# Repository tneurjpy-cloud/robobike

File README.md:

https://github.com/tneurjpy-cloud/robobike
| Supported Targets | ESP32-C3 |
| ----------------- | -------- |

ROBOBIKE: Autonomous Self-Balancing Bicycle Robot  
Copyright 2026.11.05    Masayuki Tanaami      ROBOBIKEJP    Japan  

ESP-IDF components and tools paths depend on installation location  

* Control Logic
The ROBOBIKE utilizes a dual-loop control system: an outer steering PD loop and an inner roll rate feedback loop to achieve self-balancing via counter-steering.

## Control System Architecture

```mermaid
graph TD
    %% 目標値の入力
    In((str_target)) -- "目標値" --> Sum1((+))

    subgraph OuterLoop [外側：ステアリングPD制御]
        Sum1 -- "偏差" --> GainP[Pゲイン]
        Sum1 -- "偏差" --> Diff[微分+LPF]
        
        GainP --> Sum2((+))
        Diff --> Sum2
    end

    Sum2 -- "目標ロール速度" --> Sum3((+))

    subgraph InnerLoop [内側：ロール速度FB]
        IMU[IMU_roll実測] -. "−" .-> Sum3
        Sum3 -- "偏差" --> GainW[ロールゲイン]
        GainW -- "更新量" --> Integ["積分 & 逆操舵<br>(str_out -= 更新量)"]
    end

    %% 出力とフィードバック
    Integ --> OutP[ステアリング出力 str_out]
    OutP -. "フィードバック" .-> Sum1
    
    OutP --> Limit[リミッタ]
    Limit --> PWM((PWM出力))

    %% スタイルの設定
    style OuterLoop fill:#fdfdfd,stroke:#333
    style InnerLoop fill:#f0f7ff,stroke:#0052cc
    style Integ fill:#e1f5fe,stroke:#01579b

```
## Getting Started

This project is based on "Captive Portal Example".  
Development should be done using ESP-IDF v6.0  
Please install the ESP-IDF extension in VS-Code before building this project.  
  
* How to set up IntelliSense in VS Code:  
(1) Install the ESP-IDF Extension.  
(2) (Ctrl+Shift+P)Run the command "ESP-IDF: Add vscode configuration folder".  
(3) Perform a Build to generate necessary configuration files.  
-----------------------------------------------------------  
* Settings from menuconfig are saved to \project\sdkconfig  
* Change via menuconfig, KCONFIG Name:  
    Flash size : 4MB  
    Partition Table : Custom Partition Table CSV  
        CSV file : partitions.csv  
    configUSE_TRACE_FACILITY : checked  
    configGENERATE_RUN_TIME_STATS : checked
    configTICK_RATE_HZ : 100
* For debug with GDB, delete "launch.json"
    Full Clean
    Select Target to esp32c3 via USB JTAG
    Select COM port, Build and flash
    Power down the target and perform a complete system reboot.
    OpenOCD Server, select "Eclipse CDT..."
    Full Clean
    Slelect Target to esp32c3 via USB JTAG
    Select COM port, Build and flash
    Power down the target and perform a complete system reboot.
    OpenOCD Server, select "Eclipse CDT..."
-----------------------------------------------------------  

* Change Log  
```text
Date        CODE    DATA    Description
------------------------------------------------------------------------------------------------
2026.11.10  1044       6    Chg: Fix the drift on starting, Speed-adaptive gain
2026.11.04  1043       6    Add: Check PCBA ver 06, use SPI
2026.09.27  1042       6    Add: Test mode on every reset
2026.09.13  1041       6    Dbg: Fix mobile file selection issue on OTA
2026.09.11  1040       6    Dbg: Stop servo PWM during OTA
2026.09.10  1038       6    Dbg: Accept OTA by smartphone
2026.09.02  1037       6    Chg: Captive portal handler(for iPhone)
2026.08.28  1036       6    Chg: Sleep time, minor changes for auto circling mode
2026.07.05  1033       4    Add: Data monitor and its related files.
2026.06.05  1032       4    Dbg: LED control configTICK_RATE_HZ:100
2026.05.26  1031       4    Chg: Servo PWM Rising Times. Lo-pass filter T
2026.05.19  1030    1022    Chg: Axis polarity inversion / No use GPIO Int. for Task
                            Dbg: Monitor.html  
2026.05.06  1029    1022    Chg: 3ms 1-shot soft timer -> 4ms espTimer / STR cmd Polarity +: left
                            Add: Ota, Data monitor.
                            Chg: esp-idf v5.4.1-->> v6.0.1
2026.04.07  1028    1022    Add: WiFi AP Ch. randomize
2026.03.31  1027    1021    Add: BACK cmd, SV EN Cont. heapless buffer
2026.03.20  1025    1021    Mov: GPIO definitions from servo.c to project.h
2026.03.01  1024    1021    Add: IMU data API, 
                            Dbg: Calibration
2026.02.09  1023    1021    Add: Auto circling On/Off, restore SLEEP function
2026.01.20  1022    1021    Add: Speed buttons to control UI, add only_data
2026.01.17  1021    1021    Add: Auto circling
2026.01.11  1020    1020    The 1st release
2025.12.10  1017    1015    Ex1 step: converted to float (smooth side stand movement)
2025.11.29  1016    1015    Add: Steering slide bar
2025.11.11  1014    1014    Suppress UI scaling, add adjustment items, update stop sequence
2025.10.28  1011    1011    Update: Adjustment screen
```

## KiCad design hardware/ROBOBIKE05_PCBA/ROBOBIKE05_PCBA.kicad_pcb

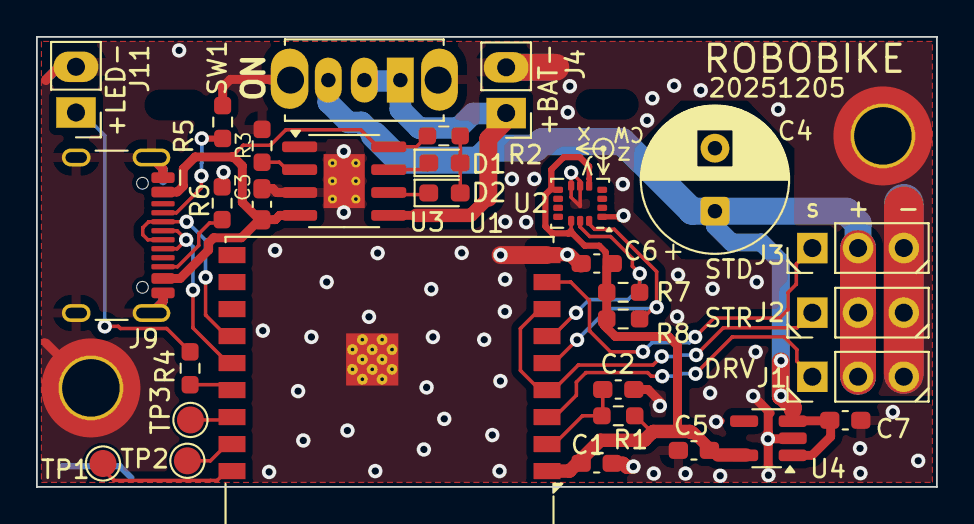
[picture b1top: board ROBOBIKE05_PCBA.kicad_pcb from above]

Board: 2 copper layers, 50.0 x 25.0 mm, 33 parts (0 on the bottom side), 24 nets.

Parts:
C1, C5, C6: 10u; C_0603_1608Metric_Pad1.08x0.95mm_HandSolder
C2, C7: 0.1u; C_0603_1608Metric_Pad1.08x0.95mm_HandSolder
C3: 1u; C_0603_1608Metric_Pad1.08x0.95mm_HandSolder
C4: 470u; CP_Radial_D8.0mm_P3.50mm
D1: LED 0603 RED; LED_0603_1608Metric_Pad1.05x0.95mm_HandSolder
D2: LED 0603 BLUE; LED_0603_1608Metric_Pad1.05x0.95mm_HandSolder
H1, H2: MountingHole_Pad; MountingHole_3.2mm_M3_ISO14580_Pad_TopBottom
J1, J2, J3: 3P PIN HEADER; PinHeader_1x03_P2.54mm_Vertical
J4, J11: WIRING HOLE; PinHeader_1x02_P2.54mm_Vertical
J9: USB_C_Receptacle_USB2.0_16P; USB_C_Receptacle_HCTL_HC-TYPE-C-16P-01A
R1: 47K; R_0603_1608Metric_Pad0.98x0.95mm_HandSolder
R2, R3: 1K; R_0603_1608Metric_Pad0.98x0.95mm_HandSolder
R4: 100; R_0603_1608Metric_Pad0.98x0.95mm_HandSolder
R5, R6, R7, R8: 5.1K; R_0603_1608Metric_Pad0.98x0.95mm_HandSolder
SW1: SS12D07VG4 087; SW_Slide_SPDT_Straight_CK_OS102011MS2Q
TP1, TP2, TP3: TestPoint_Pad_D1.5mm
U1: ESP32-C3-WROOM-02-N4; ESP32-C3-WROOM-02
U2: ICM-42607-P; LGA-16_3x3mm_P0.5mm_LayoutBorder3x5y
U3: TP4056-42-ESOP8; SOIC-8-1EP_3.9x4.9mm_P1.27mm_EP2.29x3mm_ThermalVias
U4: DS8562; SOT-23-5_HandSoldering

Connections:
+3V3: C1.1, C5.1, C6.1, R1.1, R7.2, R8.2, U1.1 (3V3), U2.5 (VDDIO), U2.8 (VDD), U2.12 (VDDIO), U4.5 (VO)
+4V: C4.1, C7.1, J1.2, J2.2, J3.2, SW1.3 (C), U4.1 (VI), U4.3 (EN)
EN: C2.1, R1.2, U1.2 (EN)
GND: C1.2, C2.2, C3.2, C4.2, C5.2, C6.2, C7.2, H1.1, H2.1, J1.3, J2.3, J3.3, J4.2, J9.A1 (GND), J9.B1 (GND), J9.S1 (SHIELD), J11.2, R3.1, R5.1, R6.1, SW1.4 (FR), U1.9 (GND), U1.19 (GND-PAD), U2.1 (AP_AD0), U2.6 (GND), U2.7 (FSYNC), U3.1 (NTC), U3.3 (GND), U3.9 (EXPAD), U4.2 (GND)
LED1: R4.1, U1.15 (IO3)
unnamed: D1.2 (A), D2.2 (A), R2.1
unnamed: D1.1 (K), U3.7 (CHRG)
unnamed: D2.1 (K), U3.6 (FULL)
unnamed: J4.1, SW1.1 (A), SW1.2 (B), U3.5 (BAT)
unnamed: J9.A5 (CC1), R5.2
unnamed: J9.B5 (CC2), R6.2
unnamed: J11.1, R4.2
unnamed: TP1.1, U1.18 (IO0)
unnamed: TP2.1, U1.17 (IO1)
unnamed: TP3.1, U1.16 (IO2)
unnamed: C3.1, J9.A4 (VBUS), J9.B4 (VBUS), R2.2, U3.4 (VIN), U3.8 (CE)
unnamed: R3.2, U3.2 (PROG)
SCL: R7.1, U1.6 (IO7), U2.13 (AP_SCL)
SDA: R8.1, U1.5 (IO6), U2.14 (AP_SDA)
SV_DRV: J1.1, U1.3 (IO4)
SV_STD: J3.1, U1.8 (IO9)
SV_STR: J2.1, U1.4 (IO5), U1.7 (IO8)
UD+: J9.A6 (D+), J9.B6 (D+), U1.14 (IO19)
UD-: J9.A7 (D-), J9.B7 (D-), U1.13 (IO18)

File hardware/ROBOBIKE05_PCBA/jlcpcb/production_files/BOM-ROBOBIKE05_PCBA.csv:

Comment,Designator,Footprint,LCSC,Quantity
0.1u,"C2,C7",C_0603_1608Metric_Pad1.08x0.95mm_HandSolder,C1591,2
TP4056-42-ESOP8,U3,SOIC-8-1EP_3.9x4.9mm_P1.27mm_EP2.29x3mm_ThermalVias,C16581,1
1K,"R2,R3",R_0603_1608Metric_Pad0.98x0.95mm_HandSolder,C21190,2
100,R4,R_0603_1608Metric_Pad0.98x0.95mm_HandSolder,C22775,1
LED 0603 RED,D1,LED_0603_1608Metric_Pad1.05x0.95mm_HandSolder,C2286,1
5.1K,"R5,R6,R7,R8",R_0603_1608Metric_Pad0.98x0.95mm_HandSolder,C25804,4
USB_C_Receptacle_USB2.0_16P,J9,USB_C_Receptacle_HCTL_HC-TYPE-C-16P-01A,C2765186,1
47K,R1,R_0603_1608Metric_Pad0.98x0.95mm_HandSolder,C2907042,1
ESP32-C3-WROOM-02-N4,U1,ESP32-C3-WROOM-02,C2934560,1
SS12D07VG4 087,SW1,SW_Slide_SPDT_Straight_CK_OS102011MS2Q,C2939726,1
470u,C4,CP_Radial_D8.0mm_P3.50mm,C2960234,1
LED 0603 BLUE,D2,LED_0603_1608Metric_Pad1.05x0.95mm_HandSolder,C2986058,1
3P PIN HEADER,"J1,J2,J3",PinHeader_1x03_P2.54mm_Vertical,C49257,3
ICM-42607-P,U2,LGA-16_3x3mm_P0.5mm_LayoutBorder3x5y,C5129967,1
DS8562,U4,SOT-23-5_HandSoldering,C5884114,1
1u,C3,C_0603_1608Metric_Pad1.08x0.95mm_HandSolder,C6119818,1
10u,"C1,C5,C6",C_0603_1608Metric_Pad1.08x0.95mm_HandSolder,C6119842,3

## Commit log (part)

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2026-04-22 1029 start
2026-04-22 1029logo
2026-04-22 use control.c
2026-04-24 1029 Chg Timer
2026-04-24 1029
2026-04-24 weberver.cを分解
2026-04-25 static file handlers into common
2026-05-22 1031 4ms IMU gain debug
2026-05-22 I2c asynchronous
2026-05-23 str cmd speed adjust
2026-05-23 skew600us
2026-05-24 diff Lopass coeff chg
2026-05-25 Brownout detector
2026-05-25 1031
2026-05-25 STOP shorten wait
2026-05-25 GDB usage
2026-06-04 1032 dbg LED drive
2026-06-05 configTICK_RATE_HZ=100Hz
2026-06-05 Add Off/On after OTA
2026-06-19 use external Interrupt
2026-06-20 chg macro
2026-06-20 use 2-stage timer int
2026-06-21 4-stage PWM frame/get small endian IMU data
2026-06-21 Lamp Low 8->32
2026-06-22 debug delay duty setup
2026-06-22 remove sch
2026-06-24 IMU read debug servo INTERLEAVED
2026-06-24 dbg std
2026-06-24 450us
2026-06-25 0625
2026-06-26 SV_POS ADC logging
2026-06-28 chg sync objet for cmd task
2026-06-28 Bode Plotter
2026-06-30 add description of plotter
